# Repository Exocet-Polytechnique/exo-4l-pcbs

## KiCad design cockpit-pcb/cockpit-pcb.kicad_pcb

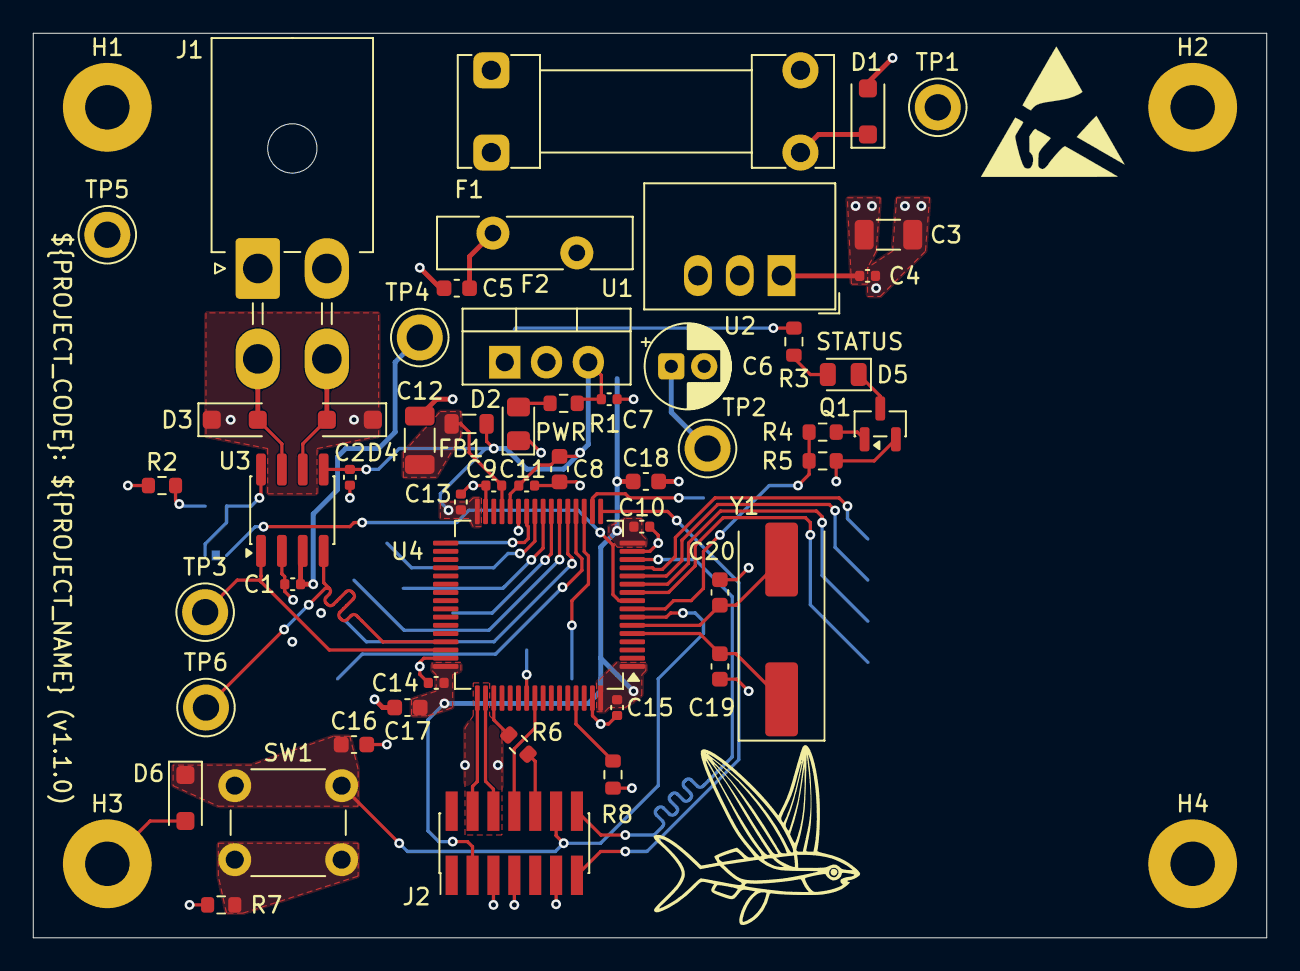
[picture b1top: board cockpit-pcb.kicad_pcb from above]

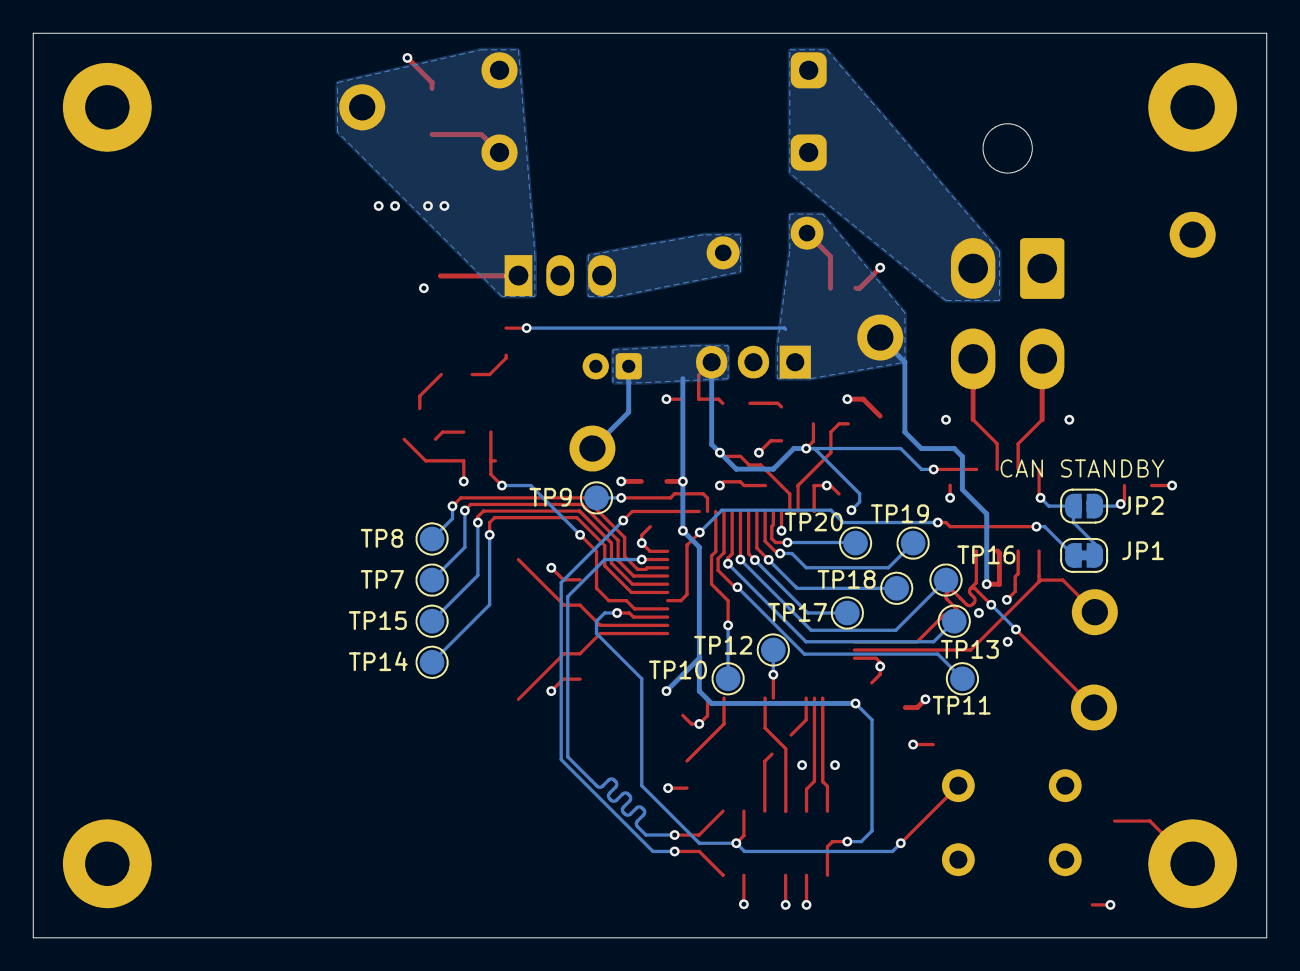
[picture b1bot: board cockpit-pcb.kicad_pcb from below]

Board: 4 copper layers, 75.0 x 55.0 mm, 74 parts (16 on the bottom side), 45 nets.

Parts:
C1, C2, C4, C7, C10, C11, C13, C14, C15: 100n; C_0402_1005Metric
C3, C12: 10u; C_1206_3216Metric
C5: 470n; C_0603_1608Metric
C6: 47u; CP_Radial_D5.0mm_P2.00mm
C8, C16, C17, C18: 2.2u; C_0603_1608Metric
C9: 10n; C_0402_1005Metric
C19, C20: 30p; C_0603_1608Metric
D1: SMF33A; D_SOD-123F
D2: KT-0805G; LED_0805_2012Metric_Pad1.15x1.40mm_HandSolder
D3, D4: SMF4L48CA; D_SOD-123F
D5: KT-0805Y; LED_0805_2012Metric
D6: SMF5.0A; D_SOD-123F
F1: Fuse Holder; Fuseholder_Clip-5x20mm_Littelfuse_111_Lateral_P18.80x5.00mm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
F2: MF-R090; PTC_Bourns_MF-R090
FB1: GZ2012D101TF; L_0805_2012Metric
H1, H2, H3, H4: 2.7mm; MountingHole_2.7mm_Pad
J1: Network Connector; Connector_Molex_0353180420
J2: STDC14; PinHeader_2x07_P1.27mm_Vertical_SMD
JP1: SolderJumper_2_Bridged; SolderJumper-2_P1.3mm_Bridged_RoundedPad1.0x1.5mm
JP2: SolderJumper_2_Open; SolderJumper-2_P1.3mm_Open_RoundedPad1.0x1.5mm
Q1: AO3400A; SOT-23
R1: 1k; R_0603_1608Metric
R2, R4, R7: 100; R_0603_1608Metric
R3, R5: 1.2k; R_0603_1608Metric
R6: 47; R_0603_1608Metric
R8: 10k; R_0603_1608Metric
SW1: SW_Push; SW_PUSH_6mm
SYM1: SYM_ESD_Large; ESD-Logo_8.9x8mm_SilkScreen
SYM2: SYM_Logo_Exocet
TP1, TP2, TP4: 5005; TestPoint_Keystone_5005-5009_Compact
TP3: 5121; TestPoint_Keystone_5005-5009_Compact
TP5: 5006; TestPoint_Keystone_5005-5009_Compact
TP6: 5009; TestPoint_Keystone_5005-5009_Compact
TP7, TP8, TP9, TP10, TP11, TP12, TP13, TP14, TP15, TP16, TP17, TP18, TP19, TP20: Pad; TestPoint_Pad_D1.5mm
U1: LM3940; TO-220-3_Vertical
U2: R-78K5.0-1.0; Converter_DCDC_RECOM_R-78K-1.0_THT
U3: TJA1042T-3; SOIC-8_3.9x4.9mm_P1.27mm
U4: STM32G474RBT6; LQFP-64_10x10mm_P0.5mm
Y1: X49SM8MSD2SC; Crystal_SMD_HC49-SD

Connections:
+3.3V: C2.2, C6.1, C7.1, C8.2, C10.1, C11.2, C13.1, C14.1, C15.1, C17.1, C18.1, FB1.1, J2.3 (VCC), R1.1, TP2.1 (1_1), U1.3 (OUT), U3.5 (VIO), U4.1 (VBAT), U4.16 (VDD), U4.28 (VREF+), U4.32 (VDD), U4.48 (VDD), U4.64 (VDD)
+5V: C1.1, C5.1, F2.2, R3.1, TP4.1 (1_1), U1.1 (IN), U3.3 (VCC)
+24V: C3.1, C4.1, D1.1 (K), F1.2, TP1.1 (1_1), U2.1 (IN)
/STM32 Base Layout/CAN_H: D3.2 (A2), J1.3 (CAN_H), U3.7 (CANH)
/STM32 Base Layout/CAN_L: D4.2 (A2), J1.4 (CAN_L), U3.6 (CANL)
/STM32 Base Layout/CAN_RX: TP6.1 (1_1), U3.4 (RXD), U4.45 (FDCAN1_RX)
/STM32 Base Layout/CAN_STANDBY: JP1.1 (A), U4.9 (PC1)
/STM32 Base Layout/CAN_TX: TP3.1 (1_1), U3.1 (TXD), U4.46 (FDCAN1_TX)
/STM32 Base Layout/OSC_IN: C19.1, U4.5 (RCC_OSC_IN), Y1.1
/STM32 Base Layout/OSC_OUT: C20.1, U4.6 (RCC_OSC_OUT), Y1.2
/STM32 Base Layout/STATUS_LED: R4.1, R5.1, U4.8 (PC0)
/STM32 Base Layout/T_JCLK/T_SWCLK: J2.6 (JCLK/SWCLK), U4.50 (SYS_JTCK-SWCLK)
/STM32 Base Layout/T_JTDI: J2.10 (JTDI/NC), R6.2
/STM32 Base Layout/T_JTDO/T_SWO: J2.8 (JTDO/SWO), U4.56 (SYS_JTDO-SWO)
/STM32 Base Layout/T_JTMS/T_SWDIO: J2.4 (JTMS/SWDIO), U4.49 (SYS_JTMS-SWDIO)
/STM32 Base Layout/T_NRST: C16.1, D6.1 (K), J2.12 (~RST), SW1.1, U4.7 (PG10)
/STM32 Base Layout/T_VCP_RX: J2.13 (VCP_RX), U4.17 (LPUART1_RX)
/STM32 Base Layout/T_VCP_TX: J2.14 (VCP_TX), U4.14 (LPUART1_TX)
GND: C1.2, C2.1, C3.2, C4.2, C5.2, C6.2, C7.2, C8.1, C9.2, C10.2, C11.1, C12.2, C13.2, C14.2, C15.2, C16.2, C17.2, C18.2, C19.2, C20.2, D1.2 (A), D2.1 (K), D3.1 (A1), D4.1 (A1), D6.2 (A), H1.1 (1_1), H2.1 (1_1), H3.1 (1_1), H4.1 (1_1), J1.1 (GND), J2.5 (GND), J2.7 (GND), J2.11 (GNDDetect), Q1.2 (S), R2.1, R5.2, R7.2, R8.2, TP5.1 (1_1), U1.2 (GND), U2.2 (GND), U3.2 (GND), U4.15 (VSS), U4.27 (VSSA), U4.31 (VSS), U4.47 (VSS), U4.63 (VSS)
unnamed: D2.2 (A), R1.2
unnamed: D5.2 (A), R3.2
unnamed: D5.1 (K), Q1.3 (D)
unnamed: F1.1, J1.2 (+24V)
unnamed: JP1.2 (B), JP2.1 (A), U3.8 (STB)
unnamed: JP2.2 (B), R2.2
unnamed: Q1.1 (G), R4.2
unnamed: R7.1, SW1.2
unnamed: F2.1, U2.3 (OUT)
unnamed: TP7.1 (1_1), U4.12 (PA0)
unnamed: TP8.1 (1_1), U4.13 (PA1)
unnamed: TP9.1 (1_1), U4.18 (PA4)
unnamed: TP10.1 (1_1), U4.19 (PA5)
unnamed: TP11.1 (1_1), U4.20 (PA6)
unnamed: TP13.1 (1_1), U4.21 (PA7)
unnamed: R6.1, U4.51 (SYS_JTDI)
unnamed: TP18.1 (1_1), U4.24 (PB0)
unnamed: TP19.1 (1_1), U4.25 (PB1)
unnamed: TP20.1 (1_1), U4.26 (PB2)
unnamed: R8.1, U4.61 (PB8)
unnamed: TP14.1 (1_1), U4.10 (PC2)
unnamed: TP15.1 (1_1), U4.11 (PC3)
unnamed: TP16.1 (1_1), U4.22 (PC4)
unnamed: TP17.1 (1_1), U4.23 (PC5)
unnamed: TP12.1 (1_1), U4.55 (PD2)
unnamed: C9.1, C12.1, FB1.2, U4.29 (VDDA)

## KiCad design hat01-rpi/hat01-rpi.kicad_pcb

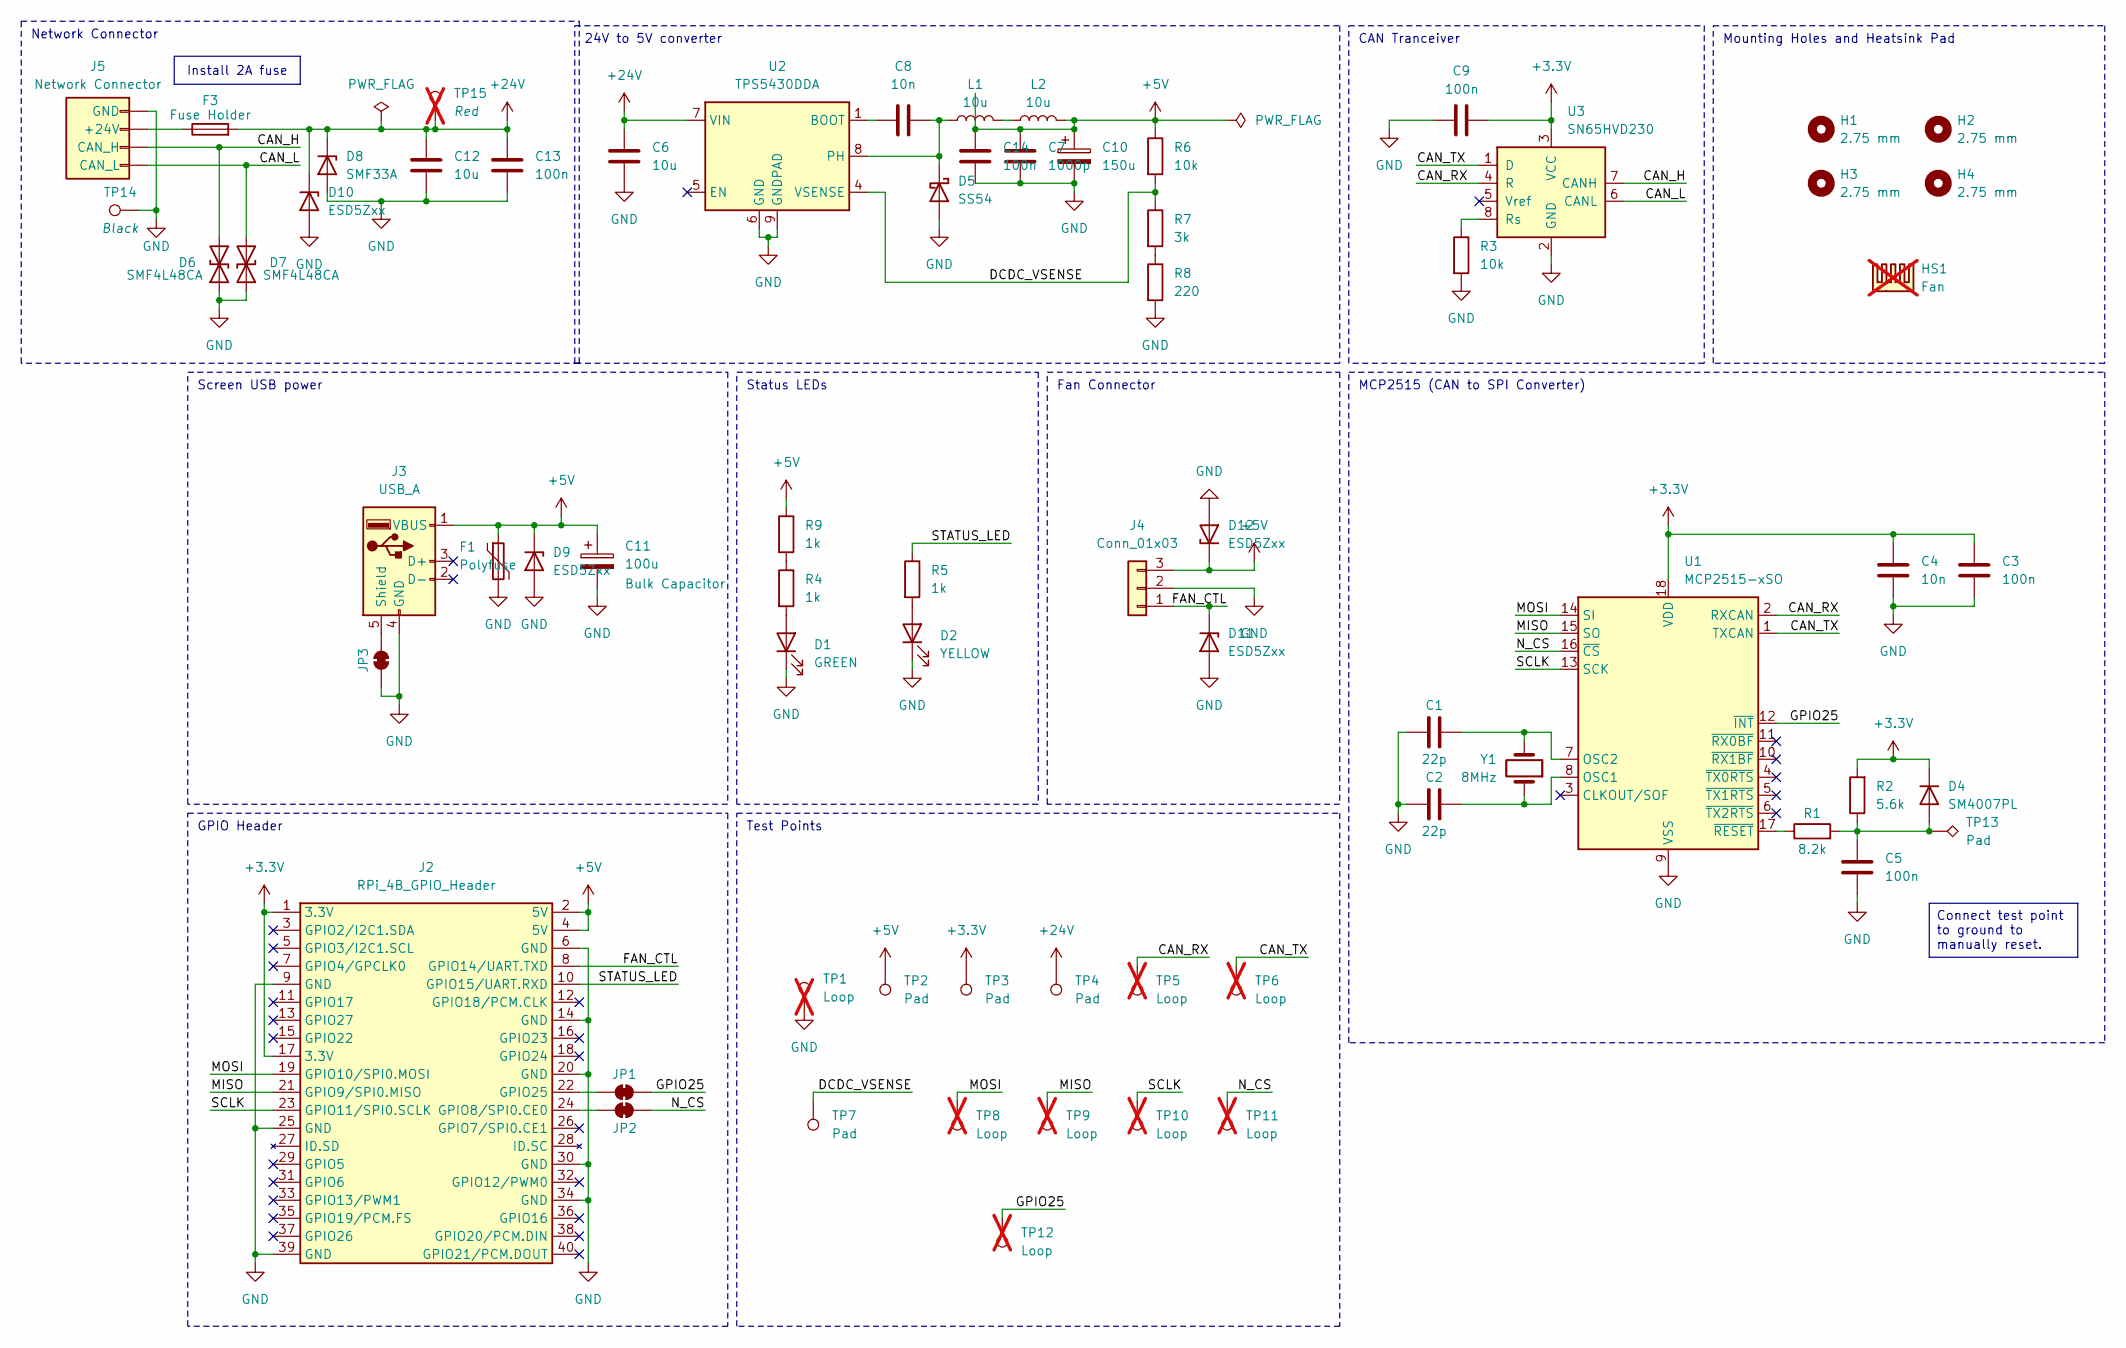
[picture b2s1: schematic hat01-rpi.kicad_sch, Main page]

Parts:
C1, C2: 22p; C_0402_1005Metric; JLCPCB C1555
C3, C5, C9: 100n; C_0402_1005Metric_Pad0.74x0.62mm_HandSolder; JLCPCB C1525
C4, C8: 10n; C_0402_1005Metric_Pad0.74x0.62mm_HandSolder; JLCPCB C15195
C6: 10u; C_1206_3216Metric_Pad1.33x1.80mm_HandSolder; JLCPCB C13585
C7: 1000p
C10: 150u; CP_Elec_6.3x7.7; JLCPCB C7471880
C11: 100u; CP_Radial_D8.0mm_P3.50mm
C12: 10u; C_1206_3216Metric
C13: 100n; C_0402_1005Metric
C14: 100n
D1: GREEN; LED_0805_2012Metric_With_Annotations; JLCPCB C2297
D2: YELLOW; LED_0805_2012Metric_With_Annotations; JLCPCB C2296
D4: SM4007PL; D_SOD-123F; JLCPCB C64898
D5: SS54; D_SMA_Handsoldering; JLCPCB C22452
D6, D7: SMF4L48CA; D_SOD-123F
D8: SMF33A; D_SOD-123F
D9, D10, D11, D12: ESD5Zxx; D_SOD-523
F1: Polyfuse
F3: Fuse Holder; Fuseholder_Clip-5x20mm_Littelfuse_111_Lateral_P18.80x5.00mm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
H1, H2, H3, H4: 2.75 mm; MountingHole_2.7mm_M2.5
HS1: Fan; RPi_Fan_Mount; not fitted
J2: RPi_4B_GPIO_Header; PinSocket_2x20_P2.54mm_Vertical
J3: USB_A; USB_A_Molex_67643_Horizontal; JLCPCB C2765194
J4: Conn_01x03; PinHeader_1x03_P2.54mm_Vertical
J5: Network Connector; Connector_Molex_0353180420
JP1, JP2, JP3: SolderJumper_2_Bridged; SolderJumper-2_P1.3mm_Bridged_RoundedPad1.0x1.5mm
L1, L2: 10u; L_Changjiang_FXL0630; JLCPCB C167223
R1: 8.2k; R_0603_1608Metric_Pad0.98x0.95mm_HandSolder; JLCPCB C25981
R2: 5.6k; R_0603_1608Metric_Pad0.98x0.95mm_HandSolder; JLCPCB C23189
R3, R6: 10k; R_0603_1608Metric_Pad0.98x0.95mm_HandSolder; JLCPCB C25804
R4, R5, R9: 1k; R_0402_1005Metric_Pad0.72x0.64mm_HandSolder; JLCPCB C11702
R7: 3k; R_0603_1608Metric_Pad0.98x0.95mm_HandSolder; JLCPCB C4211
R8: 220; R_0402_1005Metric; JLCPCB C25091
TP1, TP5, TP6, TP8, TP9, TP10, TP11, TP12: Loop; TestPoint_Keystone_5005-5009_Compact; not fitted
TP2, TP3, TP4, TP7, TP13: Pad; TestPoint_Pad_D1.5mm
TP14: 5006; TestPoint_Keystone_5005-5009_Compact
TP15: 5005; TestPoint_Keystone_5005-5009_Compact; not fitted
U1: MCP2515-xSO; SOIC-18W_7.5x11.6mm_P1.27mm; JLCPCB C153782
U2: TPS5430DDA; TI_SO-PowerPAD-8_ThermalVias; JLCPCB C9864
U3: SN65HVD230; SOIC-8_3.9x4.9mm_P1.27mm; JLCPCB C12084
Y1: 8MHz; Crystal_SMD_HC49-SD; Part Name X49SM8MSD2SC; JLCPCB C12674

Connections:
+3.3V: C3.1, C4.1, C9.1, D4.1 (K), J2.1 (3.3V), J2.17 (3.3V), R2.2, TP3.1 (1_1), U1.18 (VDD), U3.3 (VCC)
+5V: C7.1, C10.1, C11.1, C14.1, D9.1 (K), D12.1 (K), F1.1, J2.2 (5V), J2.4 (5V), J3.1 (VBUS), J4.3, L2.2, R6.1, R9.1, TP2.1 (1_1)
+24V: C6.1, C12.1, C13.1, D8.1 (K), D10.1 (K), F3.2, TP4.1 (1_1), TP15.1 (1_1), U2.7 (VIN)
/CAN_H: D6.2 (A2), J5.3 (CAN_H), U3.7 (CANH)
/CAN_L: D7.2 (A2), J5.4 (CAN_L), U3.6 (CANL)
/CAN_RX: TP5.1 (1_1), U1.2 (RXCAN), U3.4 (R)
/CAN_TX: TP6.1 (1_1), U1.1 (TXCAN), U3.1 (D)
/DCDC_VSENSE: R6.2, R7.1, TP7.1 (1_1), U2.4 (VSENSE)
/FAN_CTL: D11.1 (K), J2.8 (GPIO14/UART.TXD), J4.1
/GPIO25: JP1.2 (B), TP12.1 (1_1), U1.12 (~INT)
/MISO: J2.21 (GPIO9/SPI0.MISO), TP9.1 (1_1), U1.15 (SO)
/MOSI: J2.19 (GPIO10/SPI0.MOSI), TP8.1 (1_1), U1.14 (SI)
/N_CS: JP2.2 (B), TP11.1 (1_1), U1.16 (~CS)
/SCLK: J2.23 (GPIO11/SPI0.SCLK), TP10.1 (1_1), U1.13 (SCK)
/STATUS_LED: J2.10 (GPIO15/UART.RXD), R5.1
GND: C1.1, C2.1, C3.2, C4.2, C5.2, C6.2, C7.2, C9.2, C10.2, C11.2, C12.2, C13.2, C14.2, D1.1 (K), D2.1 (K), D5.2 (A), D6.1 (A1), D7.1 (A1), D8.2 (A), D9.2 (A), D10.2 (A), D11.2 (A), D12.2 (A), F1.2, J2.6 (GND), J2.9 (GND), J2.14 (GND), J2.20 (GND), J2.25 (GND), J2.30 (GND), J2.34 (GND), J2.39 (GND), J3.4 (GND), J4.2, J5.1 (GND), JP3.1 (A), R3.2, R8.2, TP1.1 (1_1), TP14.1 (1_1), U1.9 (VSS), U2.6 (GND), U2.9 (GNDPAD), U3.2 (GND)
unnamed: D1.2 (A), R4.2
unnamed: D2.2 (A), R5.2
unnamed: C5.1, D4.2 (A), R1.2, R2.1, TP13.1 (1_1)
unnamed: C8.2, D5.1 (K), L1.1, U2.8 (PH)
unnamed: J2.24 (GPIO8/SPI0.CE0), JP2.1 (A)
unnamed: J2.22 (GPIO25), JP1.1 (A)
unnamed: J3.5 (Shield), JP3.2 (B)
unnamed: F3.1, J5.2 (+24V)
unnamed: L1.2, L2.1
unnamed: R4.1, R9.2
unnamed: R7.2, R8.1
unnamed: C2.2, U1.8 (OSC1), Y1.1
unnamed: C1.2, U1.7 (OSC2), Y1.2
unnamed: R1.1, U1.17 (~RESET)
unnamed: C8.1, U2.1 (BOOT)
unnamed: R3.1, U3.8 (Rs)

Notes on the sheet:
CAN Tranceiver
Mounting Holes and Heatsink Pad
MCP2515 (CAN to SPI Converter)
Fan Connector
Test Points
Screen USB power
GPIO Header
24V to 5V converter
Status LEDs
Network Connector
Connect test point to ground to manually reset.
Install 2A fuse

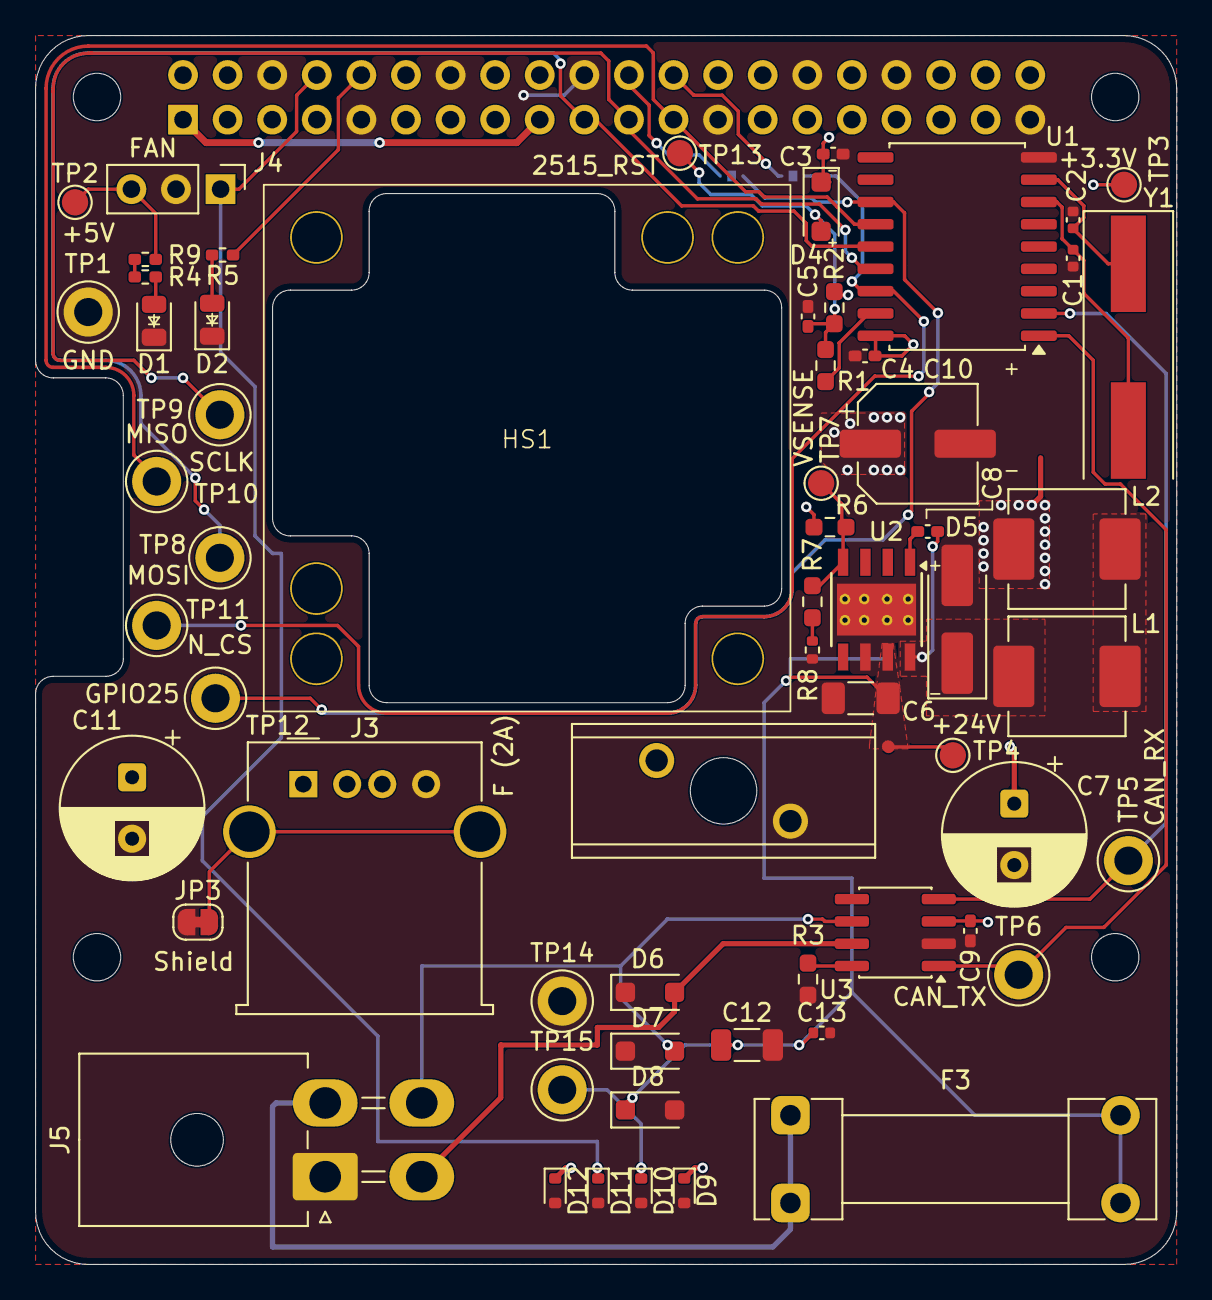
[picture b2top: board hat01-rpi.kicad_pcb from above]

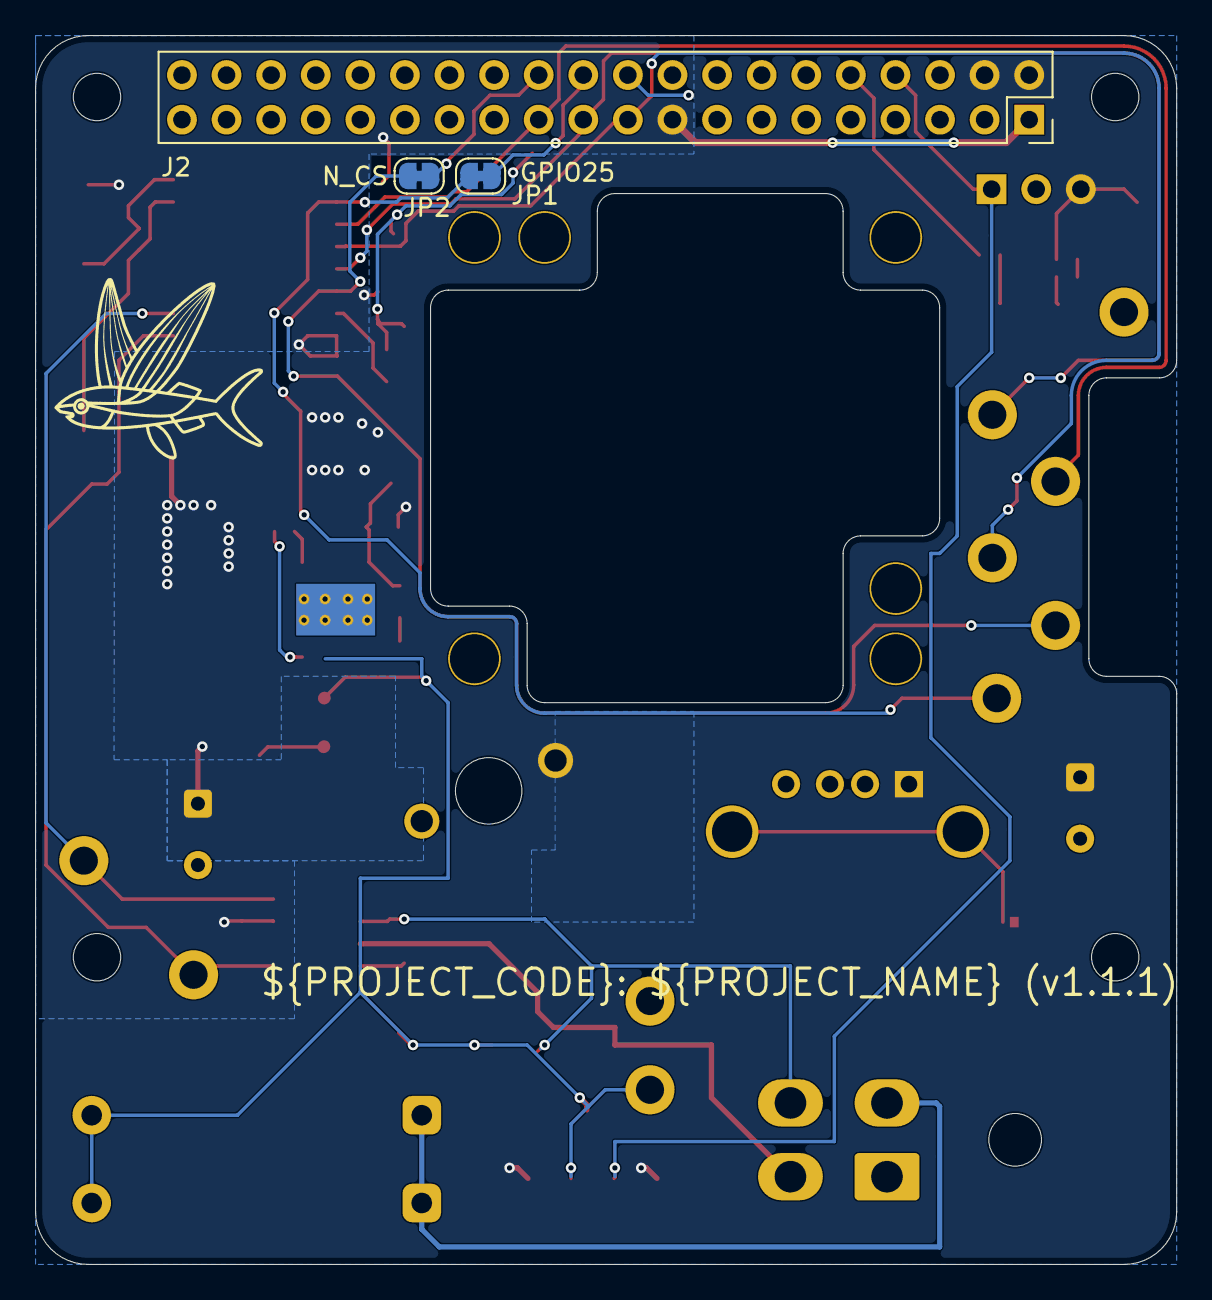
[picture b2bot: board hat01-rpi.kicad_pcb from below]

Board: 2 copper layers, 65.0 x 70.0 mm, 68 parts (3 on the bottom side), 32 nets.
